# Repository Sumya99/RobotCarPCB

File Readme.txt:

1. To check JLCPCB tracking number:

https://htm.sf-express.com/hk/en/dynamic_function/waybill/#search/bill-number/SF1655080310917

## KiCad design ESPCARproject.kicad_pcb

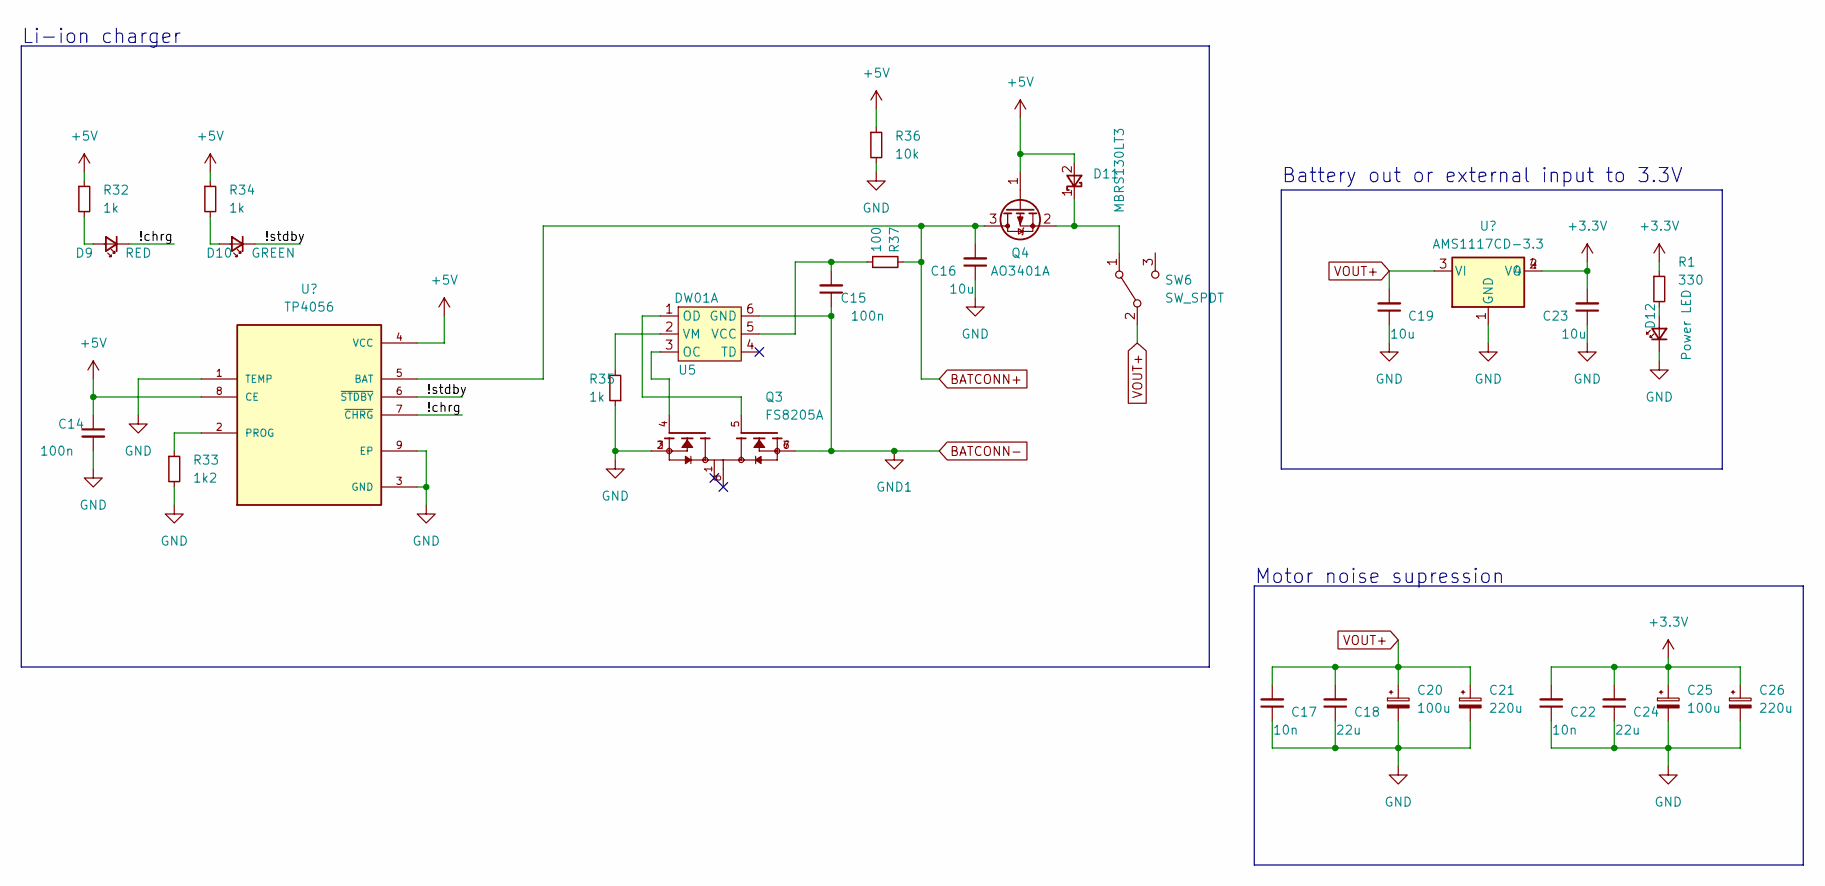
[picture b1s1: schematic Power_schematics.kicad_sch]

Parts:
C14, C15: 100n; C_0603_1608Metric_Pad1.08x0.95mm_HandSolder
C16, C19, C23: 10u; C_1206_3216Metric_Pad1.33x1.80mm_HandSolder
C17, C22: 10n; C_1206_3216Metric_Pad1.33x1.80mm_HandSolder
C18, C24: 22u; C_1206_3216Metric_Pad1.33x1.80mm_HandSolder
C20, C25: 100u; CP_Radial_Tantal_D6.0mm_P2.50mm
C21, C26: 220u; CP_Radial_Tantal_D6.0mm_P2.50mm
D9: RED; LED_0603_1608Metric_Pad1.05x0.95mm_HandSolder
D10: GREEN; LED_0603_1608Metric_Pad1.05x0.95mm_HandSolder
D11: MBRS130LT3; 403_SMB_A
D12: Power LED; LED_0603_1608Metric_Pad1.05x0.95mm_HandSolder
Q3: FS8205A; TSSOP-8_4.4x3mm_P0.65mm; PARTREV 1.7
Q4: AO3401A; SOT-23
R1: 330; R_0603_1608Metric_Pad0.98x0.95mm_HandSolder
R32, R34, R35: 1k; R_0603_1608Metric_Pad0.98x0.95mm_HandSolder
R33: 1k2; R_0603_1608Metric_Pad0.98x0.95mm_HandSolder
R36: 10k; R_0603_1608Metric_Pad0.98x0.95mm_HandSolder
R37: 100; R_0603_1608Metric_Pad0.98x0.95mm_HandSolder
SW6: SW_SPDT; SW_spdt _slide
U4: TP4056; SOP127P600X175-9N
U5: DW01A; SOT-23-6
U6: AMS1117CD-3.3; SOT-223

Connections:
+3.3V: C22.2, C23.2, C24.2, C25.1, C26.1, R1.1, U6.2 (VO), U6.4; also elsewhere on the board
+5V: C14.1, D11.2 (A), Q4.1 (G), R32.1, R34.1, R36.1, U4.4 (VCC), U4.8 (CE); also elsewhere on the board
/Power/!chrg: D9.1 (K), U4.7 (~CHRG)
/Power/!stdby: D10.1 (K), U4.6 (~STDBY)
BATCONN+: C16.2, Q4.3 (D), R37.2, U4.5 (BAT); also elsewhere on the board
BATCONN-: C15.1, Q3.6, Q3.7, U5.6 (GND); also elsewhere on the board
GND: C14.2, C16.1, C17.1, C18.1, C19.1, C20.2, C21.2, C22.1, C23.1, C24.1, C25.2, C26.2, D12.1 (K), Q3.2, Q3.3, R33.2, R35.1, R36.2, U4.1 (TEMP), U4.3 (GND), U4.9 (EP), U6.1 (GND); also elsewhere on the board
unnamed: D9.2 (A), R32.2
unnamed: D10.2 (A), R34.2
unnamed: D11.1 (K), Q4.2 (S), SW6.1 (A)
unnamed: D12.2 (A), R1.2
unnamed: R33.1, U4.2 (PROG)
unnamed: Q3.4, U5.3 (OC)
unnamed: Q3.5, U5.1 (OD)
unnamed: C15.2, R37.1, U5.5 (VCC)
unnamed: R35.2, U5.2 (VM)
VOUT+: C17.2, C18.2, C19.2, C20.1, C21.1, SW6.2 (B), U6.3 (VI); also elsewhere on the board

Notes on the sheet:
Motor noise supression
Battery out or external input to 3.3V
Li-ion charger

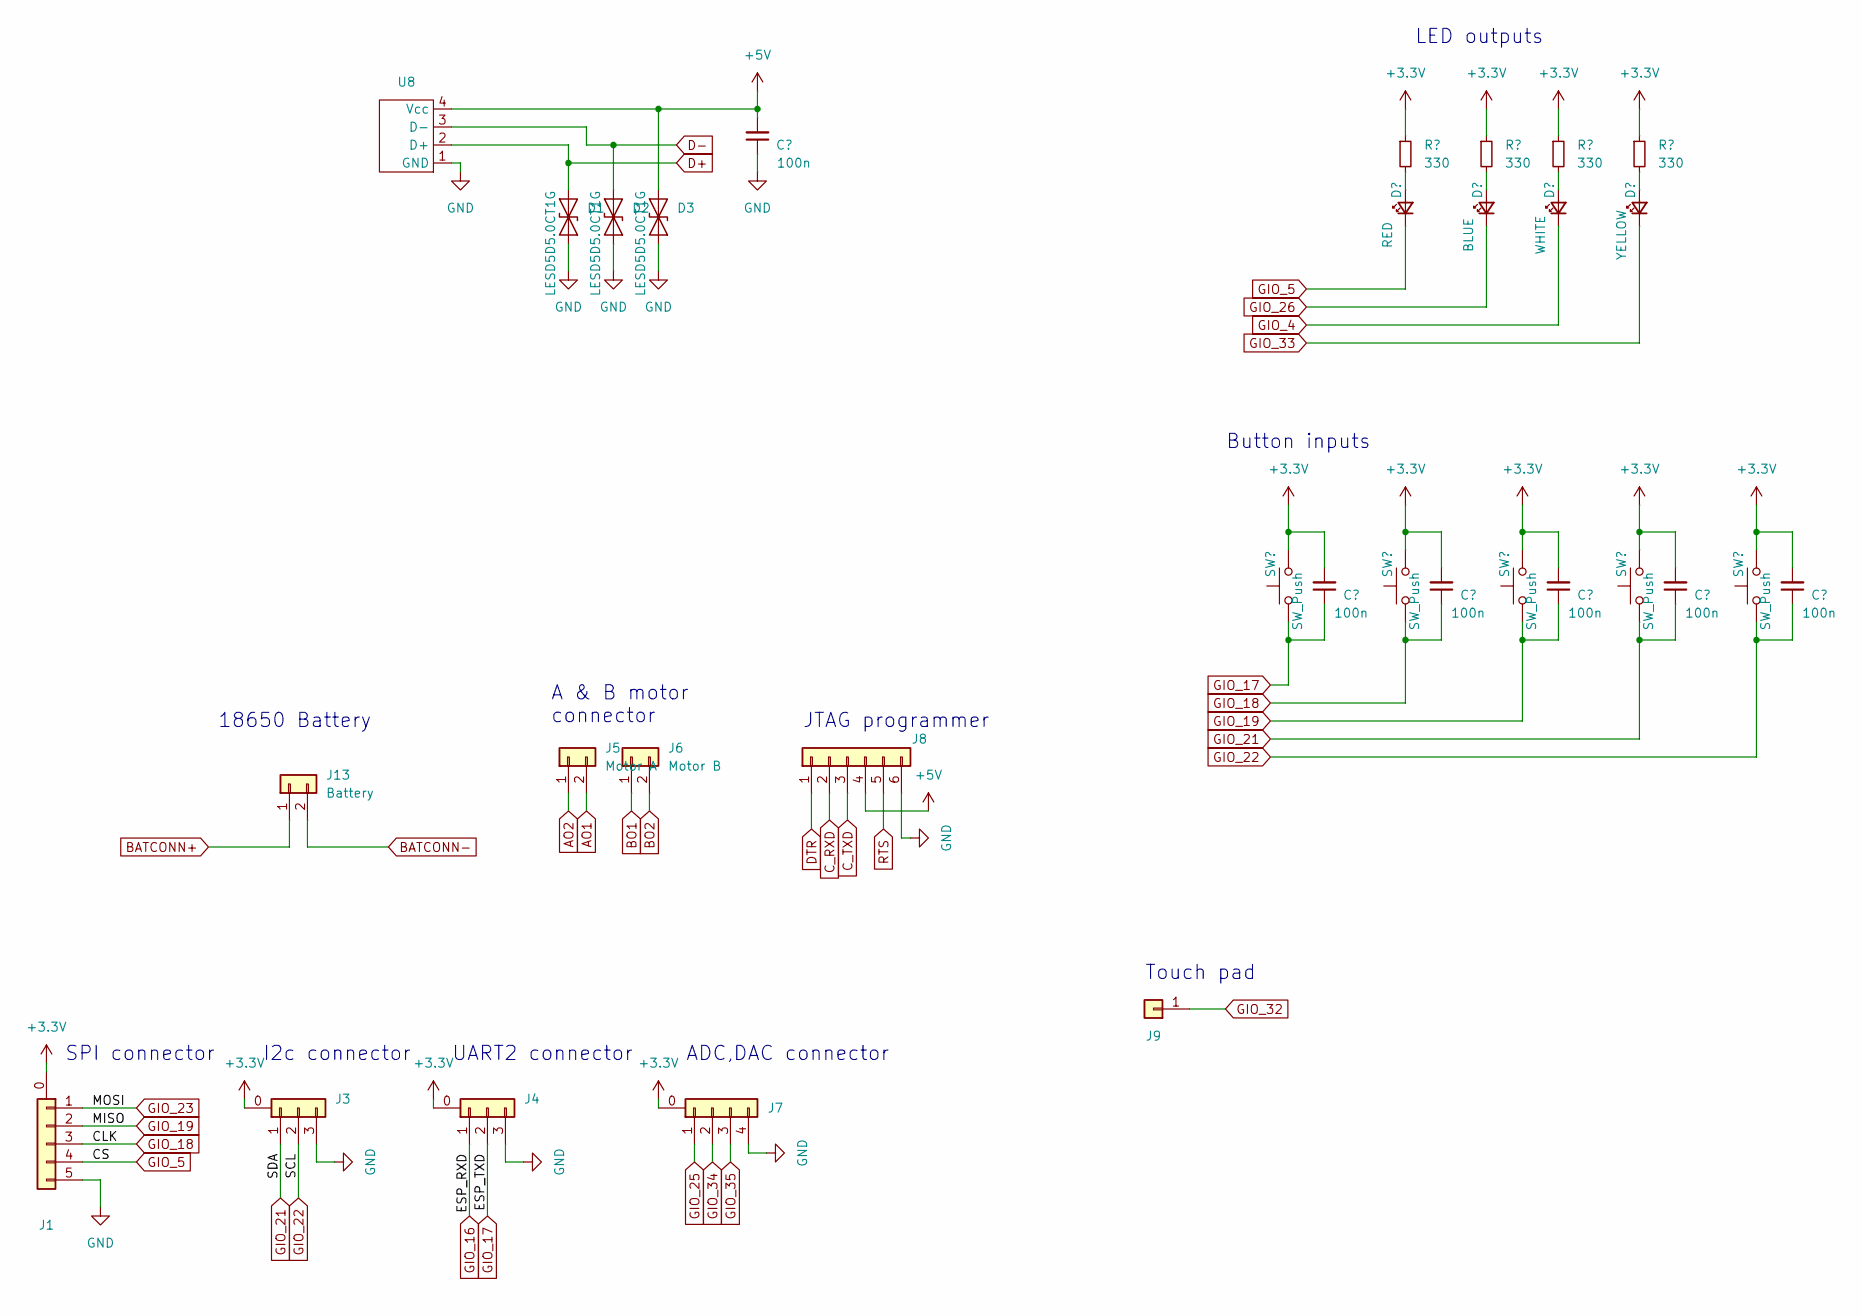
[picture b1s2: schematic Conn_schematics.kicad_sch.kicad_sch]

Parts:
C1, C2, C3, C4, C5, C6: 100n; C_0603_1608Metric_Pad1.08x0.95mm_HandSolder
D1, D2, D3: LESD5D5.0CT1G; D_SOD-523
D5: RED; LED_0603_1608Metric_Pad1.05x0.95mm_HandSolder
D6: BLUE; LED_0603_1608Metric_Pad1.05x0.95mm_HandSolder
D7: WHITE; LED_0603_1608Metric_Pad1.05x0.95mm_HandSolder
D8: YELLOW; LED_0603_1608Metric_Pad1.05x0.95mm_HandSolder
J1: SPI; PinHeader_1x05_P2.54mm_Vertical
J3: I2c; PinHeader_1x03_P2.54mm_Vertical
J4: UART2; PinHeader_1x03_P2.54mm_Vertical
J5: Motor A; connector_2pin_5.08
J6: Motor B; connector_2pin_5.08
J7: DAC & ADC; PinHeader_1x04_P2.54mm_Vertical
J8: JTAG; PinHeader_1x06_P2.54mm_Vertical
J9: Conn_01x01; ESP_touch_pad
J13: Battery; connector_2pin_5.08
R4, R5, R6, R7: 330; R_0603_1608Metric_Pad0.98x0.95mm_HandSolder
SW1, SW2, SW3, SW4, SW5: SW_Push; SW_Push_SPST_NO_Alps_SKRK
U8: TypeC_254

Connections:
+3.3V: C2.2, C3.2, C4.2, C5.2, C6.2, J1.0 (Pin_1), J3.0 (Pin_1), J4.0 (Pin_1), J7.0 (Pin_1), R4.1, R5.1, R6.1, R7.1, SW1.2, SW2.2, SW3.2, SW4.2, SW5.2; also elsewhere on the board
+5V: C1.2, D3.2 (A2), J8.4, U8.4 (Vcc); also elsewhere on the board
AO1: J5.2; also elsewhere on the board
AO2: J5.1; also elsewhere on the board
BATCONN+: J13.1; also elsewhere on the board
BATCONN-: J13.2; also elsewhere on the board
BO1: J6.1; also elsewhere on the board
BO2: J6.2; also elsewhere on the board
C_RXD: J8.2; also elsewhere on the board
C_TXD: J8.3; also elsewhere on the board
D+: D1.2 (A2), U8.2 (D+); also elsewhere on the board
D-: D2.2 (A2), U8.3 (D-); also elsewhere on the board
DTR: J8.1; also elsewhere on the board
GIO_4: D7.1 (K); also elsewhere on the board
GIO_5: D5.1 (K), J1.4; also elsewhere on the board
GIO_16: J4.1; also elsewhere on the board
GIO_17: C2.1, J4.2, SW1.1; also elsewhere on the board
GIO_18: C3.1, J1.3, SW2.1; also elsewhere on the board
GIO_19: C4.1, J1.2, SW3.1; also elsewhere on the board
GIO_21: C5.1, J3.1, SW4.1; also elsewhere on the board
GIO_22: C6.1, J3.2, SW5.1; also elsewhere on the board
GIO_23: J1.1; also elsewhere on the board
GIO_25: J7.1; also elsewhere on the board
GIO_26: D6.1 (K); also elsewhere on the board
GIO_32: J9.1; also elsewhere on the board
GIO_33: D8.1 (K); also elsewhere on the board
GIO_34: J7.2; also elsewhere on the board
GIO_35: J7.3; also elsewhere on the board
GND: C1.1, D1.1 (A1), D2.1 (A1), D3.1 (A1), J1.5, J3.3, J4.3, J7.4, J8.6, U8.1 (GND); also elsewhere on the board
unnamed: D5.2 (A), R4.2
unnamed: D6.2 (A), R5.2
unnamed: D7.2 (A), R6.2
unnamed: D8.2 (A), R7.2
RTS: J8.5; also elsewhere on the board

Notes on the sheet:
ADC,DAC connector
JTAG programmer
UART2 connector
18650 Battery
LED outputs
Touch pad
I2c connector
SPI connector
Button inputs
A & B motor connector

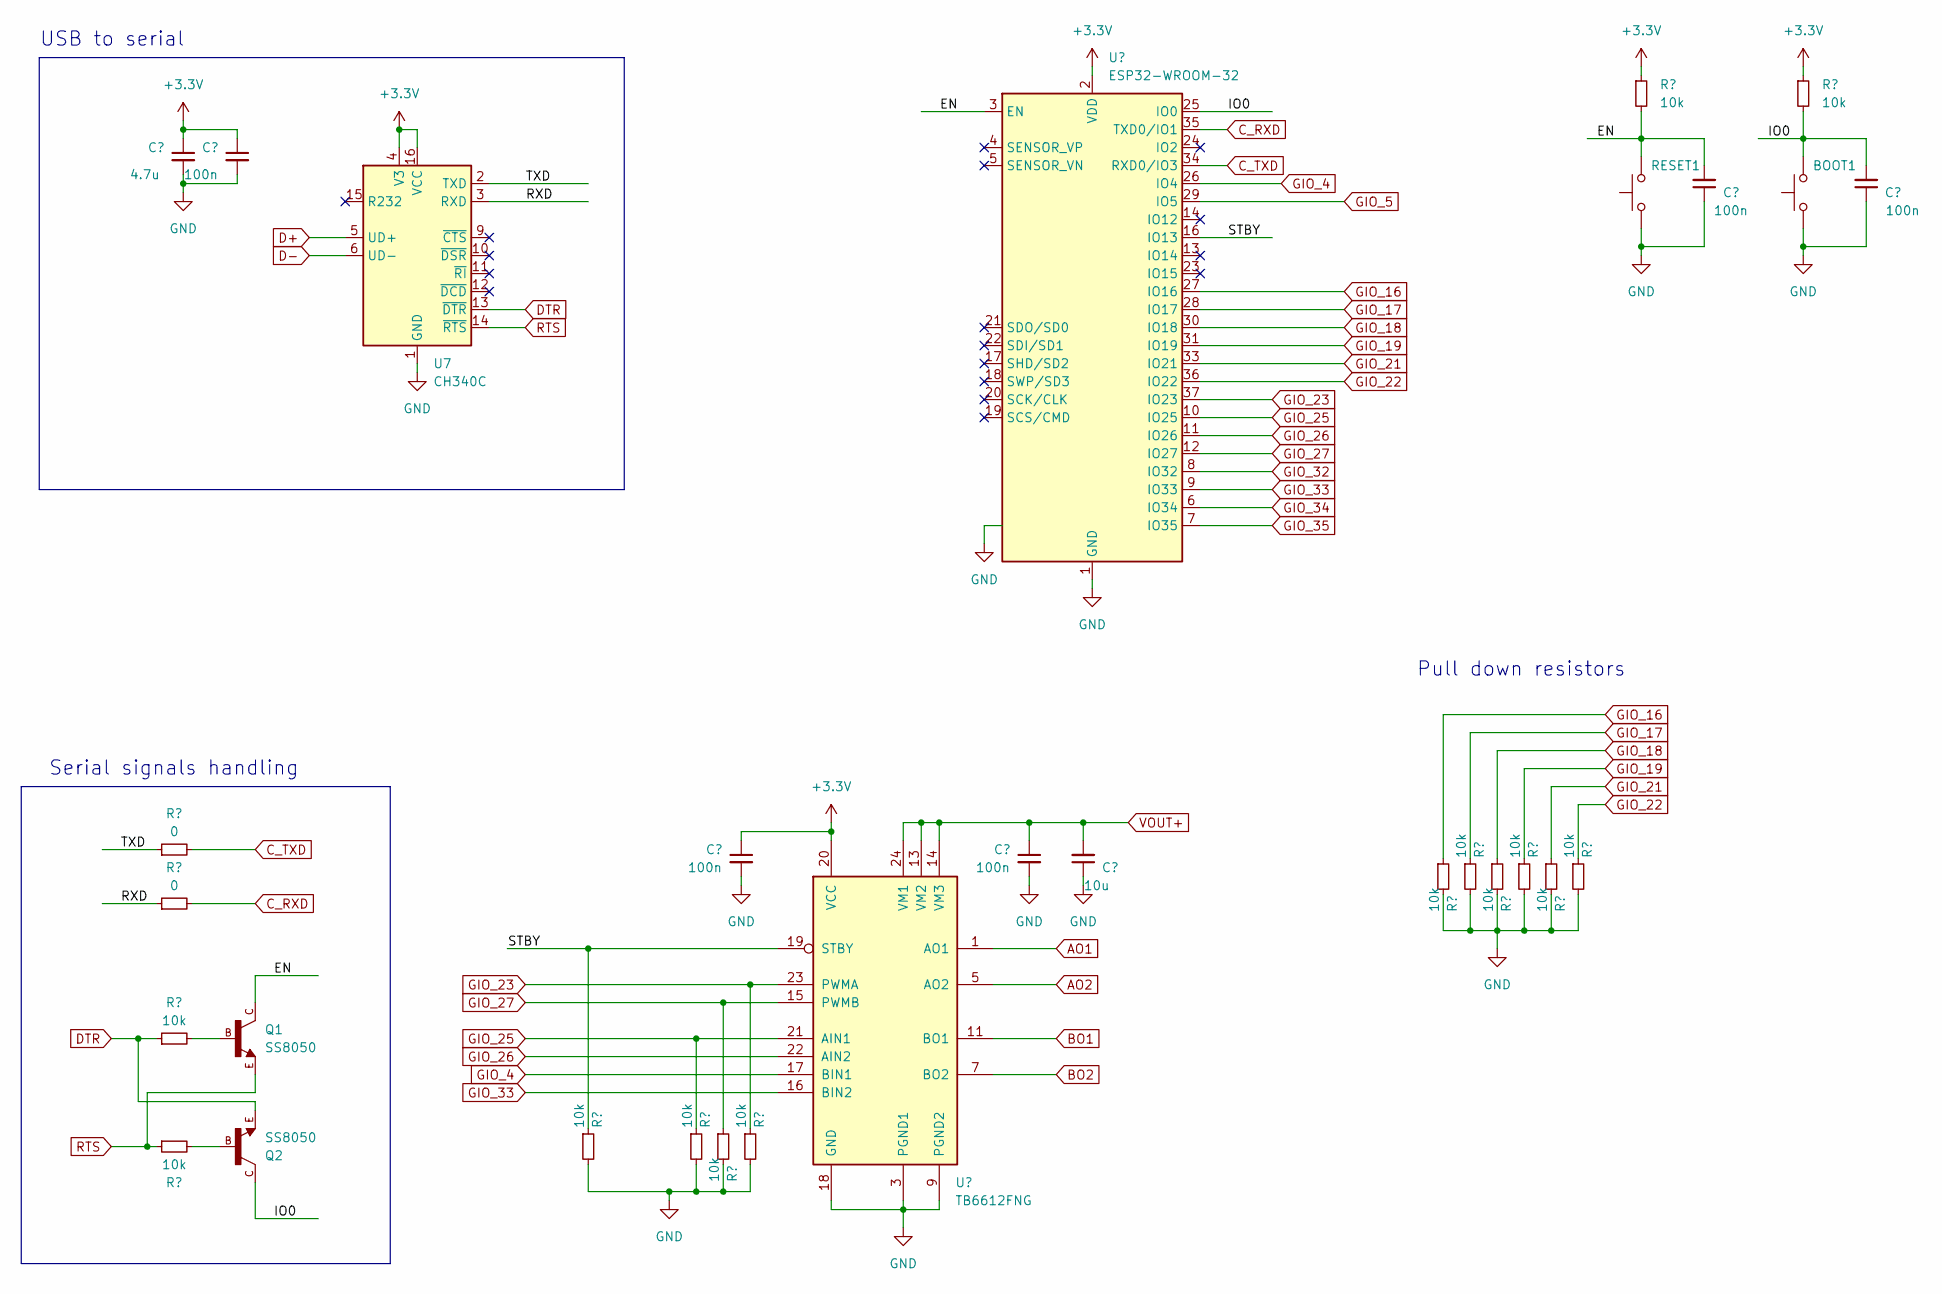
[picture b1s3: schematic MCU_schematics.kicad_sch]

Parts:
BOOT1: SW_Push; SW_Push_SPST_NO_Alps_SKRK
C7: 4.7u; C_0603_1608Metric_Pad1.08x0.95mm_HandSolder
C8, C9, C10, C12, C13: 100n; C_0603_1608Metric_Pad1.08x0.95mm_HandSolder
C11: 10u; C_1206_3216Metric_Pad1.33x1.80mm_HandSolder
Q1, Q2: SS8050; SOT-23_BEC
R10, R11: 0; R_0603_1608Metric_Pad0.98x0.95mm_HandSolder
R12, R13, R16, R20, R21, R22, R24, R25, R26, R27, R28, R29, R30, R31: 10k; R_0603_1608Metric_Pad0.98x0.95mm_HandSolder
RESET1: SW_Push; SW_Push_SPST_NO_Alps_SKRK
U2: TB6612FNG; SSOP-24_5.3x8.2mm_P0.65mm
U3: ESP32-WROOM-32
U7: CH340C; SOIC-16_3.9x9.9mm_P1.27mm

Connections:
+3.3V: C7.1, C8.1, C9.1, R30.1, R31.1, U2.20 (VCC), U3.2 (VDD), U7.4 (V3), U7.16 (VCC); also elsewhere on the board
/MCU/EN: C12.2, Q1.C, R30.2, RESET1.2, U3.3 (EN)
/MCU/IO0: BOOT1.2, C13.2, Q2.C, R31.2, U3.25 (IO0)
/MCU/RXD: R11.1, U7.3 (RXD)
/MCU/STBY: R16.1, U2.19 (STBY), U3.16 (IO13)
/MCU/TXD: R10.1, U7.2 (TXD)
AO1: U2.1 (AO1), U2.2 (AO1); also elsewhere on the board
AO2: U2.5 (AO2), U2.6 (AO2); also elsewhere on the board
BO1: U2.11 (BO1), U2.12 (BO1); also elsewhere on the board
BO2: U2.7 (BO2), U2.8 (BO2); also elsewhere on the board
C_RXD: R11.2, U3.35 (TXD0/IO1); also elsewhere on the board
C_TXD: R10.2, U3.34 (RXD0/IO3); also elsewhere on the board
D+: U7.5 (UD+); also elsewhere on the board
D-: U7.6 (UD-); also elsewhere on the board
DTR: Q2.E, R12.1, U7.13 (~DTR); also elsewhere on the board
GIO_4: U2.17 (BIN1), U3.26 (IO4); also elsewhere on the board
GIO_5: U3.29 (IO5); also elsewhere on the board
GIO_16: R24.1, U3.27 (IO16); also elsewhere on the board
GIO_17: R25.1, U3.28 (IO17); also elsewhere on the board
GIO_18: R26.1, U3.30 (IO18); also elsewhere on the board
GIO_19: R27.1, U3.31 (IO19); also elsewhere on the board
GIO_21: R28.1, U3.33 (IO21); also elsewhere on the board
GIO_22: R29.1, U3.36 (IO22); also elsewhere on the board
GIO_23: R22.1, U2.23 (PWMA), U3.37 (IO23); also elsewhere on the board
GIO_25: R20.1, U2.21 (AIN1), U3.10 (IO25); also elsewhere on the board
GIO_26: U2.22 (AIN2), U3.11 (IO26); also elsewhere on the board
GIO_27: R21.1, U2.15 (PWMB), U3.12 (IO27)
GIO_32: U3.8 (IO32); also elsewhere on the board
GIO_33: U2.16 (BIN2), U3.9 (IO33); also elsewhere on the board
GIO_34: U3.6 (IO34); also elsewhere on the board
GIO_35: U3.7 (IO35); also elsewhere on the board
GND: BOOT1.1, C7.2, C8.2, C9.2, C10.2, C11.1, C12.1, C13.1, R16.2, R20.2, R21.2, R22.2, R24.2, R25.2, R26.2, R27.2, R28.2, R29.2, RESET1.1, U2.3 (PGND1), U2.4 (PGND1), U2.9 (PGND2), U2.10 (PGND2), U2.18 (GND), U3.1 (GND), U3.15 (GND), U3.32 (NC), U3.38 (GND), U3.39 (GND), U7.1 (GND); also elsewhere on the board
unnamed: Q1.B, R12.2
unnamed: Q2.B, R13.2
RTS: Q1.E, R13.1, U7.14 (~RTS); also elsewhere on the board
VOUT+: C10.1, C11.2, U2.13 (VM2), U2.14 (VM3), U2.24 (VM1); also elsewhere on the board

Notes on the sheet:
Serial signals handling
USB to serial
Pull down resistors

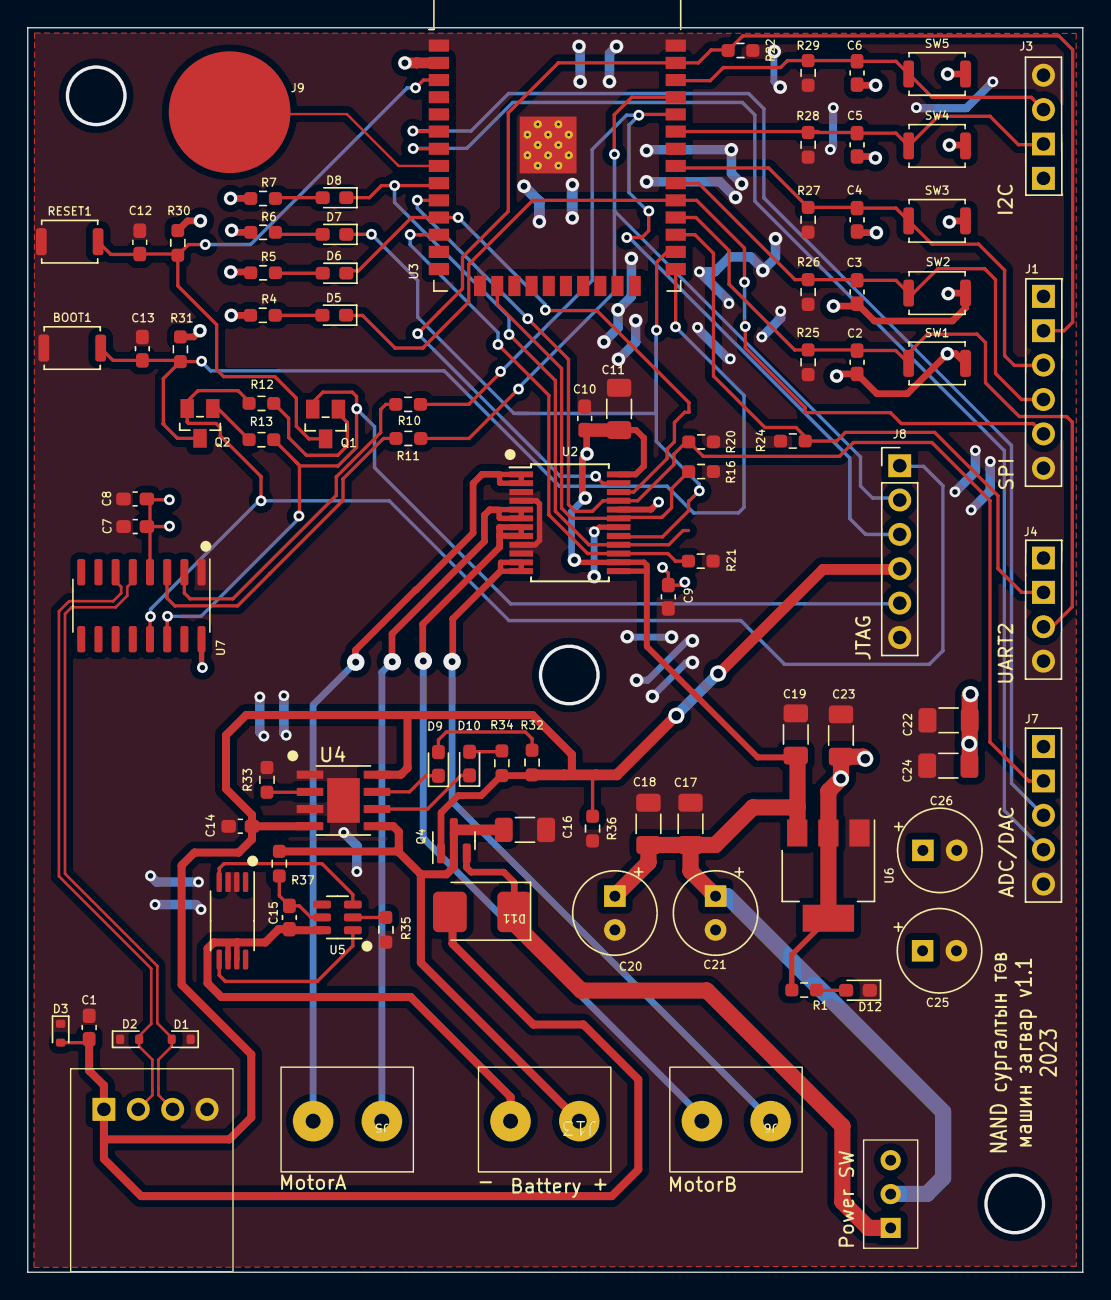
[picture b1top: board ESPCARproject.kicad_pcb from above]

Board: 2 copper layers, 78.0 x 92.0 mm, 92 parts (0 on the bottom side), 54 nets.

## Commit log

2023-11-30 first committt
2023-12-01 version 1.1
2023-12-01 edited
